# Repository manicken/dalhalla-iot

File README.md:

# Dalhalla-IoT – Modular IoT Framework

## Updates

## Overview

This is an **IoT framework** primarily targeting **ESP8266** and **ESP32** microcontrollers.  
However, the framework itself is **not bound to any specific hardware** — most of the development was actually done on **Windows (MinGW)** and later **Linux**, to take advantage of advanced debugging tools that helped isolate a **Heisenbug**.

Future candidates for porting include **Raspberry Pi Pico** and **Teensy**.

Currently, the project uses the **Arduino framework** as a base, 
but there’s essentially nothing preventing it from running **fully standalone**, 
apart from needing to provide custom drivers.

The **WiFiManager library** is used to easily flash multiple devices with firmware and register them on a network.  
This part may later evolve into something more like **Tasmota** or **ESPEasy**, simplifying device initialization.

---

## Key Features

- **Modular and lightweight architecture** 
- **HAL/DAL configuration via JSON**, mapped to an internal tree structure.
- Devices can be added/removed **without firmware rebuild** or even restarting the system.
- Unified **device abstraction layer** — each device has a unique **UID** (8-character ASCII, mapped internally to `uint64_t` for fast access).
- All devices derive from a common `Device` base class with virtual functions.
- Optional **Device Capabilities interface** planned to auto-generate documentation for each device in the GUI.

---

## JSON Configuration

Configuration is hierarchical (tree-based), supporting both **physical** and **logical/virtual** devices.

- Address paths use `:` (colon) as a separator — safe for HTTP URLs.
- Example:  
  `root:1wire:sensor1:temp`

### Example: 1-Wire Bus Groups

- Multiple 1-Wire buses can be grouped.
- Supports synchronized measurements across sensors:
  - Send `start measure` to all devices.
  - Wait defined interval.
  - Read all values simultaneously.
- Supports `refreshTime` per group or per individual device.

---

## Core Data Types

### `HALValue`
A generic type handling integers, unsigned integers, and floats consistently, simplifying read/write/compare logic.

### `ZeroCopyString`
A custom lightweight string type (similar to `std::string_view`) with additional utility:
- `SplitOffHead(char delimiter)` – substring extraction without copying.
- Direct numeric conversion (`int32`, `uint32`, `float`).
- Hex values (`0x` prefix) auto-detected.
- Used extensively to minimize heap fragmentation.

---

## Script Engine

Inspired by **ESPEasy Rules**, with plans for **event-driven execution** (not yet fully implemented, it's in a beta stage).

Scripts interact with devices via their UIDs, as defined in the JSON configuration.

**Syntax Highlights:**
- Conditionals (`if`, `then`, `elseif`, `else`, `endif`)
- Event blocks (`on`, `endon`) — planned.
- Newlines normalized to `\n`
- Supports `//` and `/* ... */` comments.
- Identifiers may include letters, digits, `_ : #`
- Numbers recognized automatically (`int`, `float`, hex).

**Example reserved keywords:**  
`if, then, do, elseif, else, endif, on, endon`

**Virtual devices** act as internal variables for flexible data handling.

---

## File Handling & Configuration Reload

- **Web-based file management** via FSBrowser for editing config and scripts.
- `CommandExecutor` (`DALHAL_CommandExecutor.cpp`) handles:
  - Config/script reload
  - Device commands
  - External access via Serial/WebSocket

### Websocket (port 82)/Serial(UART) API
Please note that the old REST API has been deprecated because its synchronous structure is incompatible with AsyncWebServer. In the future, it might be possible to make it work using the standard synchronous WebServer.

However the new Websocket API is accessed on <deviceIP>:82/ws but <deviceIP>:82 provides a simple built in GUI for basic needs

| Endpoint | Description |
|-----------|-------------|
| `hal/reloadcfg` | Reload HAL configuration |
| `hal/scripts/reload` | Reload scripts |
| `hal/scripts/start` | Start script execution |
| `hal/scripts/stop` | Stop scripts |
| `hal/getAvailableGPIOs` | List GPIOs |
| `hal/printDevices` | Print all devices |
| `hal/printLog` | Show system log |
| `hal/exec/<device_uid>` | Execute command on device |
| `hal/read/<type>/<device_uid>/<cmd>` | Read from device |
| `hal/write/<type>/<device_uid>/<value>` | Write to device |
| `system/info` | Get System Info |
| `system/reset` or `system/restart` | Execute a system restart |
| `ver` | gets build version, is not currently not updated regulary as the software is still in major development |
| `help` | Show the whole command tree |

**Types:** `bool`, `uint`, `float`, `string`, `json`  
**Device-specific commands:** e.g. read `temp` from DHT sensor.

### Windows Environment
Uses a **command loop thread** to dispatch commands to the `CommandExecutor`.

---

## Architecture Details

### Timers

Uses a modified version of **TimeAlarms**, supporting:
- Individual parameter sets per alarm.
- Safe parameter casting using `OnTickExtParameters` base class.

> https://github.com/manicken/TimeAlarms

---

## Memory Optimization and Heap Management

### JSON Loading Process
1. File read into `const char*` buffer (for zero-copy parsing via ArduinoJSON).
2. JSON document created with 1.5× file size buffer.
3. Validation ensures all mandatory fields exist.
4. Valid entries counted, marked, and loaded into an internal device array.
5. Deallocation of buffer and JSON document.

Although pointer arrays help reduce fragmentation, complete deallocation leaves large gaps (“holes”).  
A potential future solution is to convert configuration into **BSON** to allow direct loading without reallocation.

### Script Loading
- All active scripts validated sequentially.
- Only valid scripts loaded into memory for execution.
- Comments stripped before memory allocation.
- Validated scripts compiled into optimized, pre-tokenized structures for fast runtime execution.

---

## Example Files

- **HAL config example:**  
  [hal_cfg.json](https://github.com/manicken/dalhalla-io/blob/main/hal_cfg.json)
- **TimerAlarms config example:**  
  [template.json](https://github.com/manicken/dalhalla-io/blob/main/template.json)
- **Script example:**  
  [script1.txt](https://github.com/manicken/dalhalla-io/blob/main/script1.txt)

---

## Webbased WiFi configurator

[Available here](https://github.com/manicken/dalhalla-iot/tree/main/InitialCfgGui)

- Introduces a HTML + JavaScript tool as an alternative to the AP-based web portal.
- Works in Chromium-based browsers (Edge, Opera, Chrome, etc.).
- Enables configuration of Wi-Fi settings and credentials via USB-serial connection, without needing to connect to the device's AP.
- **Log output:** displays messages printed by the device in real-time.
- **Command input:** allows sending commands directly to the device.

This provides a more flexible option for local setup and testing.

## Licensing

The project currently uses **GPLv3**, to ensure it remains **fully open-source**.  
However, device registries for `root` and `i2c` are under **MIT license**, allowing third-party device extensions without forced disclosure.

Open for discussion whether the entire project should remain GPLv3 or switch fully to MIT.

---

## Future Plans

- Full event-driven script execution (beta state)
- MQTT and WebSocket(implemented) command sources.
- More advanced web UI for configuration and file management.
- Optional BSON configuration storage to eliminate heap fragmentation.
- Extended device capability introspection and GUI auto-documentation (is in a beta stage).

---

## Purpose

> The main goal is to provide a **flexible architecture for IoT devices**,  
> where configuration and logic can be changed **without recompilation**.

**dependencies**<br>
special version of TimeAlarms<br>
that can have any amount of alarms (up to 255)<br>
and also can use parameters when calling handler functions<br>
note. this dependency is included in platformio.ini and is automatically installed<br>
https://github.com/manicken/TimeAlarms <br>

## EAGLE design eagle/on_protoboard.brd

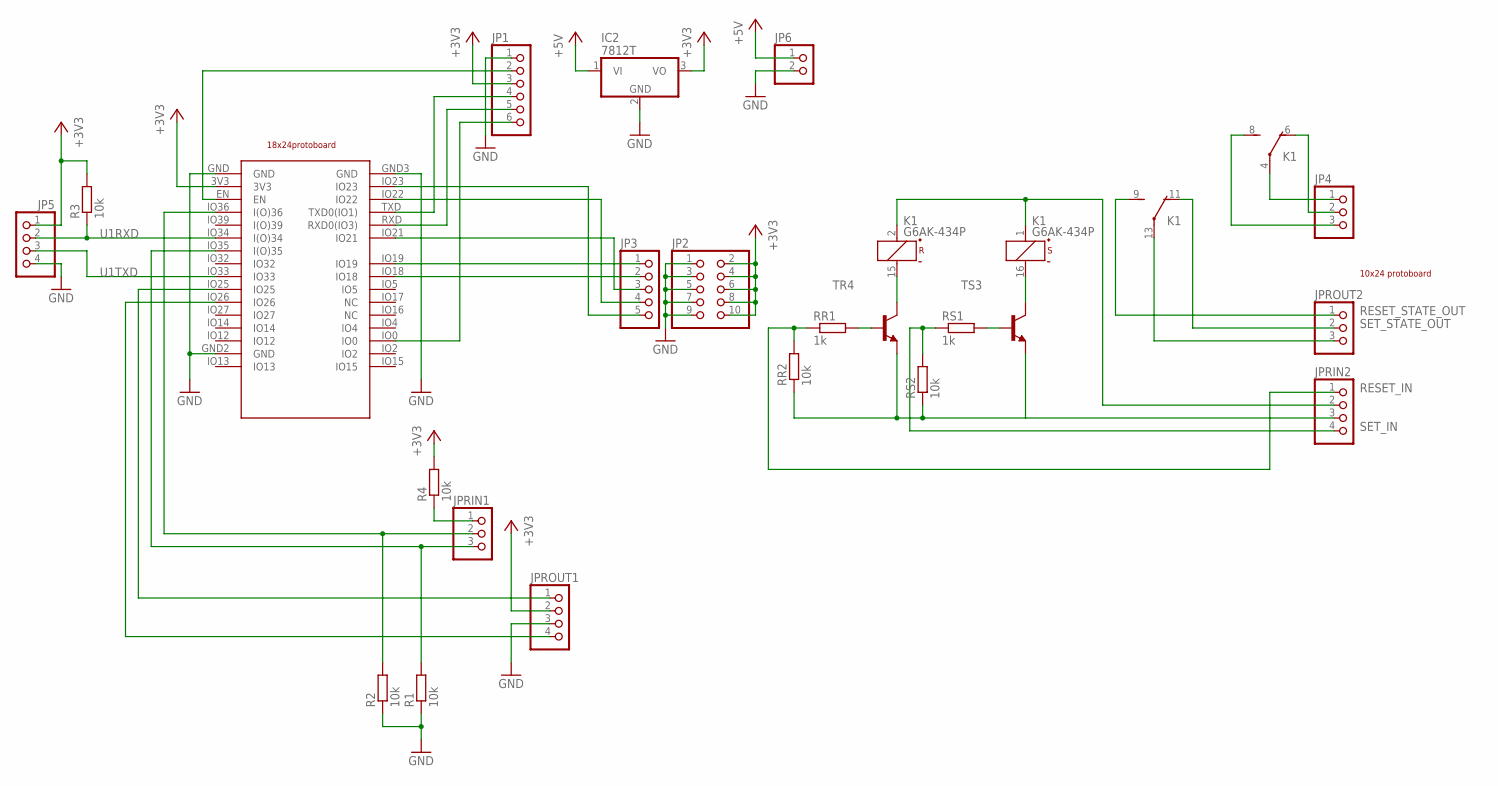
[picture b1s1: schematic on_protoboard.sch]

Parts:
ESP-32S-ADAPTER-PCB1: ESP-32S-ADAPTER-BREAKOUT; ESP-32S-ADAPTER-PCB
IC2: 7812T; TO220H
JP1: PINHD-1X6/90; 1X06/90
JP2: PINHD-2X5; 2X05
JP3: PINHD-1X5; 1X05
JP4: PINHD-1X3; 1X03
JP5: PINHD-1X4; 1X04
JP6: PINHD-1X2; 1X02
JPRIN1: PINHD-1X3; 1X03
JPRIN2: PINHD-1X4; 1X04
JPROUT1: PINHD-1X4; 1X04
JPROUT2: PINHD-1X3; 1X03
K1: G6AK-434P
R1, R2, R3, R4: 10k; R0603
RR1: 1k; R0603
RR2: 10k; R0603
RS1: 1k; R0603
RS2: 10k; R0603
TR4: -NPN-TO92-EBC; TO92-EBC
TS3: -NPN-TO92-EBC; TO92-EBC
U$1: 18X24; PROTOBOARD_18X24_HOLE
U$2: 10X24; PROTOBOARD_10X24_HOLE

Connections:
+3V3: ESP-32S-ADAPTER-PCB1.3V3, IC2.3 (VO), JP1.3, JP2.2, JP2.4, JP2.6, JP2.8, JP2.10, JP5.1, JPROUT1.2, R3.2, R4.2
+5V: IC2.1 (VI), JP6.1
GND: ESP-32S-ADAPTER-PCB1.GND, ESP-32S-ADAPTER-PCB1.GND2 (GND), ESP-32S-ADAPTER-PCB1.GND3 (GND), IC2.2 (GND), JP1.1, JP2.1, JP2.3, JP2.5, JP2.7, JP2.9, JP5.4, JP6.2, JPROUT1.3, R1.1, R2.1
unnamed: ESP-32S-ADAPTER-PCB1.EN, JP1.2
unnamed: JPRIN2.2, K1.1 (+), K1.2 (+)
unnamed: ESP-32S-ADAPTER-PCB1.TXD (TXD0(IO1)), JP1.4
unnamed: ESP-32S-ADAPTER-PCB1.RXD (RXD0(IO3)), JP1.5
unnamed: K1.15 (-), TR4.C
unnamed: ESP-32S-ADAPTER-PCB1.IO0, JP1.6
unnamed: K1.16 (-), TS3.C
unnamed: RS1.2, TS3.B
unnamed: JPRIN2.3, RR2.1, RS2.1, TR4.E, TS3.E
unnamed: JPROUT2.3, K1.13
unnamed: RR1.2, TR4.B
unnamed: ESP-32S-ADAPTER-PCB1.IO19, JP3.1
unnamed: ESP-32S-ADAPTER-PCB1.IO18, JP3.2
unnamed: ESP-32S-ADAPTER-PCB1.IO21, JP3.3
unnamed: JP4.1, K1.4
unnamed: JP4.3, K1.8 (S)
unnamed: ESP-32S-ADAPTER-PCB1.IO22, JP3.4
unnamed: ESP-32S-ADAPTER-PCB1.IO35 (I(O)35), JPRIN1.3, R1.2
unnamed: JP4.2, K1.6 (O)
unnamed: ESP-32S-ADAPTER-PCB1.IO36 (I(O)36), JPRIN1.2, R2.2
unnamed: ESP-32S-ADAPTER-PCB1.IO23, JP3.5
unnamed: JPRIN1.1, R4.1
unnamed: ESP-32S-ADAPTER-PCB1.IO25, JPROUT1.1
unnamed: ESP-32S-ADAPTER-PCB1.IO26, JPROUT1.4
RESET_IN: JPRIN2.1, RR1.1, RR2.2
RESET_STATE_OUT: JPROUT2.1, K1.9 (S)
SET_IN: JPRIN2.4, RS1.1, RS2.2
SET_STATE_OUT: JPROUT2.2, K1.11 (O)
U1RXD: ESP-32S-ADAPTER-PCB1.IO34 (I(O)34), JP5.2, R3.1
U1TXD: ESP-32S-ADAPTER-PCB1.IO33, JP5.3

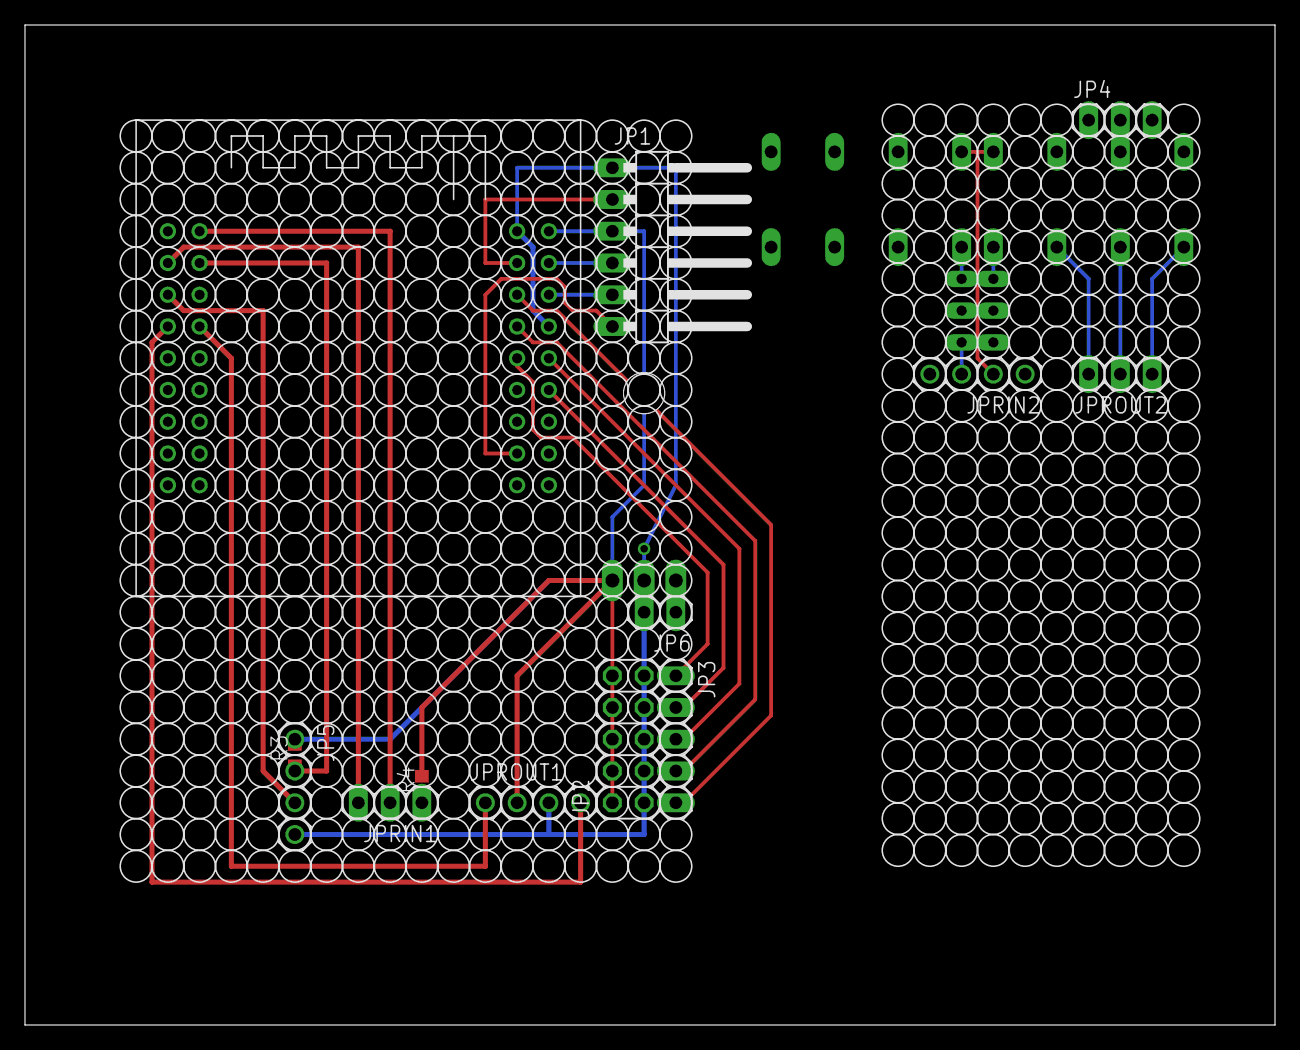
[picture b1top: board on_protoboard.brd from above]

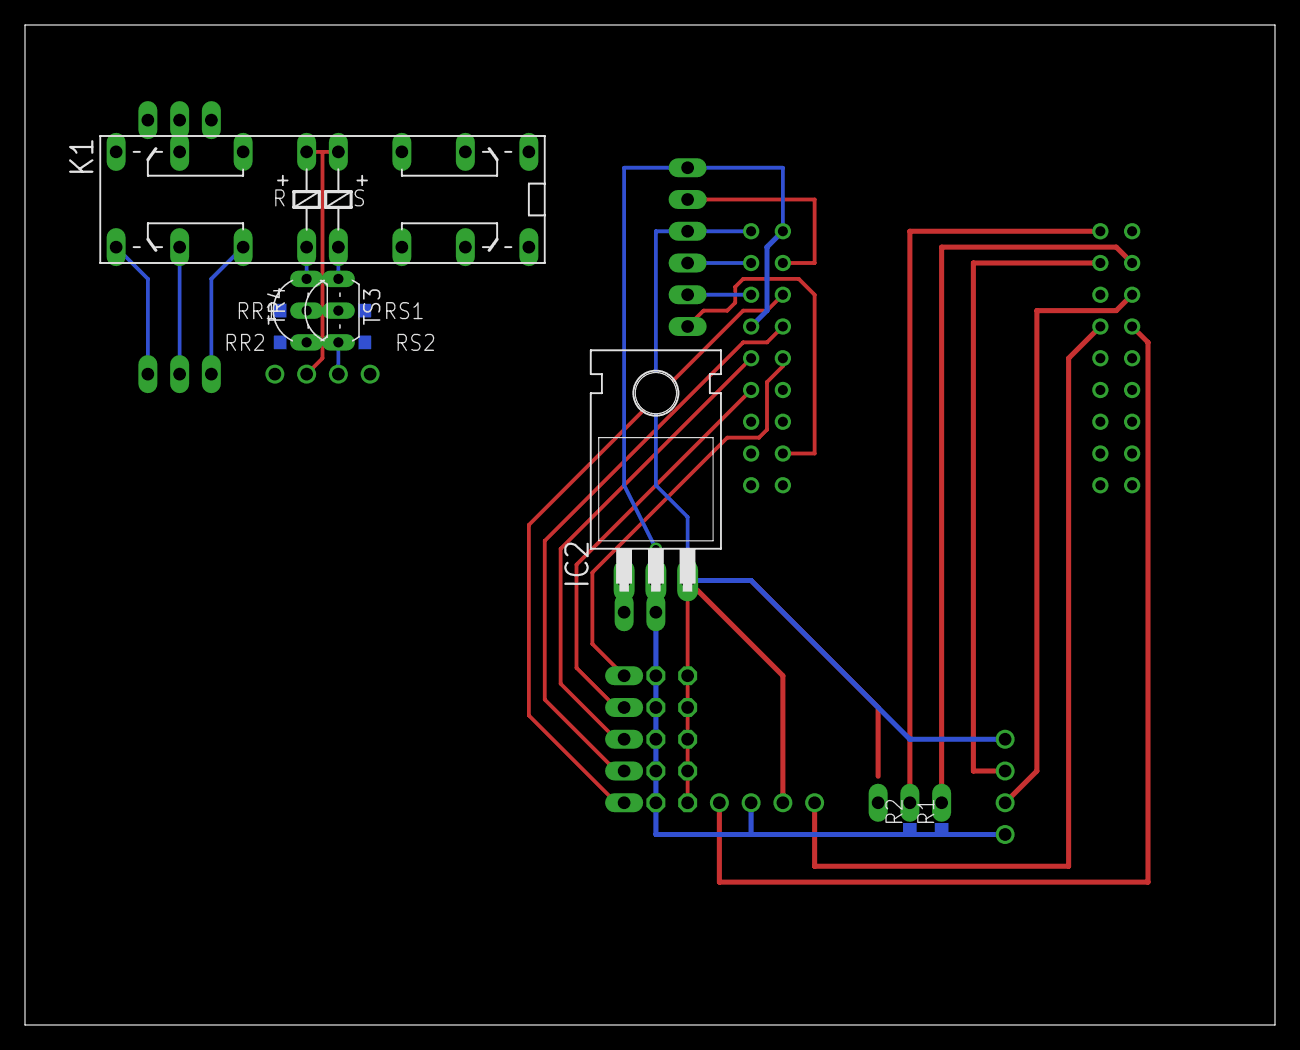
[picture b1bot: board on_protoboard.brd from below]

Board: 2 copper layers, 100.0 x 80.0 mm, 25 parts (10 on the bottom side), 33 nets.

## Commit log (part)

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2025-09-23 add I2C device name resolution for scanner
2025-09-26 scripts list.txt can now be used to define which scripts to load, if not found then script1.txt is default
2025-09-26 disabled scripts list file reading/parsing for now as there is a bug somewhere
2025-09-29 Multiscript using list.txt is now available, note default scriptname is now script.txt
2025-09-30 performance optimizations
2025-09-30 templated ParseAndTokenize have now replaced StripComments, CountTokens and Tokenize for better code maintainbility
2025-10-01 Rename Token(s) to ScriptToken(s) and make separate Token that only have col line the inherit line: ZeroCopyString->Token->ScriptToken
2025-10-01 Separating out Action and Conditions related code to own files
2025-10-01 Move all Parser and Runtime related files to subfolders
2025-10-02 non blocking startup when wifi connection fail+better webtoolui+serial halcmdexec
2025-10-28 begin working on ExtractAssignmentParts to allow func call statements
2025-11-03 refactoring cleaner code, begin to add remote fetch REST virtual device
2025-11-04 begin to work with allowing [] accessors in script engine
2025-11-06 This update removes the old CachedDeviceAccess system and introduces the lighter CachedDeviceRead implementation.
2025-11-06 Update README to include InitialCfgGui comment
2025-11-13 Fixed win_sim stubs so i can begin to work with HomeAssistant implementation using PubSubClient
2025-11-15 Futher implementations of HASS
2025-11-16 HA ++
2025-11-18 HASS ++
2025-11-19 HA Sensor entity done
2025-11-20 implement access to Hass jsonRoot so that for example device UID can be passed or other global settings
2025-11-20 uniform status state deviceuid generation
2025-11-26 fix PubSubClient so that it compiles on pc sim + other bugfixes
2025-11-27 HASS switch/button/sensor now works
2025-11-28 Fix HA device so it allow subdevices (actually type error), plus fixed Device::findInArray (device array) so when device are set to not having sub dev. and the path given has many it generate error
2025-12-01 CommandExecutor: remove usage of Request structs, error report on operation not success using device type, change to use GlobalLogger for errors
2025-12-02 cb null check
2025-12-03 better findDevice function
2025-12-03 implemented the event function for the template class
2025-12-04 move planned PWM_LEDC type, and included comment about placing items after RegistryTerminatorItem
2025-12-09 Made 1 wire temp and dht devices able to trigger events
2025-12-10 currently not working
2025-12-11 stable release
2026-01-14 fix small typo
2026-01-15 DCServo device add timeout functionality plus json cfg
2026-01-24 add LEDC_Servo device, TODO replace REST interface with proper WebSocket
2026-01-26 LEDC_Servo cfg add autoOffAfterMs, useNormValue then adjusted code
2026-01-28 add waveshare esp32-c6-zero support
2026-01-31 fixed HA number so that it properly sends back current value changed value on success, otherwise the old value is sent back. Also fixed the command path to use callback to be completely transparent o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
2026-02-05 Fixed Actuator naming bug, Updated ButtonInput to fretch value from targetDevice instead of storing toggle value locally, add WebSocketAPI Global Message Function
2026-02-13 prototype HASS DD removal of stale entities
2026-02-15 Actuator: change Motor to Drive to generalize, Created new device LatchingRelay (currently only feedback mode)
2026-02-15 Fix conflicts of globally used names
2026-02-17 add hass dd debug logging
2026-02-18 Add HA Sensor availability send non deadlock
2026-02-22 REGO600 driver use of RegDefine and OpCodeInfo instead of raw opcode + address, dalhal rego600 device uses regnamne instead of raw opcode + address
2026-02-26 Major code restructure and cleanup
2026-02-27 More code cleanup and creating better file folder structures
2026-02-28 Move dalhal devices into separate folders so that the Reactive implementation files can live beside, then implemented the reactive engine completely, TODO implement on all devices
2026-02-28 Some cleanup
2026-03-01 Add ReactiveHALValue that can emit event through a callback when the value is changed, then implemented ScriptVariableReactive
2026-03-03 Sort items
2026-03-04 Reactive implement on: LatchingRelay, LEDC_Servo & ThingSpeak
2026-03-04 implemented reactive @ ButtonInput
2026-03-04 change LEDC_Servo to more general PWM_Servo
2026-03-05 Begin with JSON Scheme structures, implemented static CheckOrGetDeviceEvents function TODO implement it on every device that uses Reactive
2026-03-07 Add API cmd printRegistry and cleared up system/info and gpio print, also fixed API web UI autodetect json which use details element
2026-03-11 Begin to refactor device registry
2026-03-12 Refactor to use DeviceCreateContext& context for all CreateFunctions and device constructors
2026-03-12 Maybe split Registry Base Define into DefineBase and RootDefine
2026-03-16 Begin to cleanup device .h files
2026-03-17 Finished Json Schema Validator, remove obsolete UseRootUID flag and usage of special type Register::DefineRoot
2026-03-18 PWM Servo Json Scheme almost done, TODO need special FieldConstraint so that i can compare two values
2026-03-19 Schema now validate Constraints
2026-03-19 Add more json schemes
2026-03-24 Fix more JsonSchemes for Script/RF433 devices
2026-03-25 REGO600 device JsonScheme done
2026-03-25 cleanup - removed comments related to ::VerifyJSON
2026-03-25 Homeassistant json scheme done
2026-03-25 remove all usage of old ValidateJSON functions, and all reg fields
2026-03-27 Can now print whole schema to the WebsocketClient as a json to use with future gui
2026-04-01 change PinFunctions into constexpressions inside a namespace PinFunc for much easier usage
2026-04-02 Split out and improved FieldString variants
2026-04-04 Now Script Events are working
2026-04-07 start to fix pc simulation code port
2026-04-08 Added additional info on JsonSchema Validations
2026-04-08 Fixed annoying bug that did happend when using virtual schema fields groups
2026-04-14 Begin to implement the new schema type structures
2026-04-14 Begin to implement the new schema type structures ++2
2026-04-15 chore: reorganize project file structure for JSON schema types + typo fix
2026-04-16 minor cleanup
2026-04-19 Progress on Schema ToJson using the new structures
2026-04-21 Optimize the generated Schema Json
2026-04-22 refactor to use the new schemadriven value extractors
2026-04-25 Refactor schema extraction: add instance-based extractors and remove static dispatch usage. Implemented on more devices
2026-04-27 fix init order problem with i2c master, plus implemented websocket system/EnterRecoveryMode command that executes directly as a failsafe against main loop locks
2026-04-29 refactor HALValue: removed as<type> replaced it with to<type> and asRaw<type> also did refactor of whole HALValue to make it consistent + added new WiFiConnection manager
2026-05-04 Make GPIO_Manager cleaner + introduced pin reservation types so that static pin reservations can be done
2026-05-06 Refactor PubSubClient to streaming RX architecture
    - Split header/payload parsing
    - Add header + complete callbacks
    - Replace std::function with function pointers + context
    - Add structured error handling
    - Reduce RAM and flash usage
2026-05-07 Refactor to use the new PSC beginPublish_fmt, lastTxTopic and lastTxTopicLength functions, inside DD Send
2026-05-13 Fix when and how HASS subscribes to topics, this fixes alot of issues
2026-05-19 Refactor - Remove use of TopicBasePath Refactor - now only storing a std::string for the hass_uid Refactor - add HALValue Printer helper to use with the Print class Refactor - Change into using new f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
2026-05-20 forgot to read hass_uid into the instance string
2026-05-21 Fix so that 1wire temp and DHTxx devices use a dataValid flag to signal when they have actually read a valid value
2026-05-21 add failsafe reset rest cmd
2026-05-22 Refactor and bug fixes * Move OTA start out of ArduinoOTA wrapper OTA.h OTA.cpp * fix data extraction bug in RF433 driver where expected uint but tried convert to const char* * Fix so that value chec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
2026-05-27 Refactor
    * Added virtual const Registry::DefineBase* GetRegistryDefine();
    this is gonna be used to get the define from a instance directly
    without the need to do a second lockup using the type
    used to fetch the sirect access function ptrs to use in CachedDeviceAccess and CachedDeviceRead
    can also be used to fetch help by only giving the device uid
    * added expected value type given to general HALValue read/write functions
2026-05-29 Wrap device registries in a struct DeviceRegistry { const Registry::Item* items; const size_t count; const char* name; const char* path; constexpr DeviceRegistry(const Registry::Item* items, const si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
    start to implement WebSocket_StreamWriter to use with the API CLI functions
    it's also to be used with the upcoming cfg editor GUI
2026-06-02 move DALHAL_ReactiveConfig delete config folder as it makes autocomplete hard while typing co to get core Split StreamWriter into StringBuilderStreamer and BlockStreamer for better separation so that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
2026-06-03 Refactor to use StringBuilderStreamer everywhere i create huge strings to be consumed by API
2026-06-04 Major refactor where all Devices: String ToString() are replaced with void PrintTo(StringBuilderStreamer& sbs) for absolute heap free allocations and fragmentation
2026-06-04 now have the following: static bool Broadcast(const char* msg, size_t len, CmdCbType type = CmdCbType::Control); static bool Broadcast(std::string &msg, CmdCbType type = CmdCbType::Control); // to be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
    changed:
    void Logger::EmitLastEntry()
    {
2026-06-04 cleanup
2026-06-08 Fix ArduinoJSON.h to proper ArduinoJson.h to make it compile on linux OS , also make sure to include ArduinoJson.h where its used to avoid include creep
2026-06-10 Template device now have all possible By FunctionName Table examples
2026-06-10 All devices that have functions by name now have Function vs Name Lockup Tables implemented 1 wire temp device and bus have own Registry defines for future proof structures and to avoid sharing data 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
2026-06-11 Remove CLI-specific virtual Device command handlers in favor of function tables
    Replace legacy Device virtual read/write/exec CLI entry points with function-table dispatch.
    Rename exec(ZeroCopyString) (previously only used by Home Assistant) to ha_apply to clarify intent as an external state update hook.
2026-06-11 Refactor CommandExecutor into hierarchical command tree dispatcher
    - Replace flat/virtual command handling with static constexpr command tree
    - Introduce recursive node-based command resolution (ExecuteNode)
    - Split command parsing into structured path (type/uid/cmd/params)
    - Standardize HAL read/write execution through function tables
    - Centralize device capability lookup via GetDeviceFunction
    - Add recursive help printer based on command tree traversal
2026-06-17 --- Major refactor --- Introduced new FunctionTable macros to make everything tidy: - DALHAL_FUNCTION_ENTRY(name, fn, help) { CE_MATCH_EMIT_STR(name), &fn, CE_EMIT_STR(help) } - DALHAL_FUNCTION_ENTRY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
    Removed/Replaced all previous used device exec/read/write functions
    with new FunctionTable en
2026-06-19 Moved Script/Device Trigger Validate function from DeviceManager to DALHAL_SCRIPT_ENGINE_Parser_Triggers
2026-06-19 TODO make script exec() function work again
2026-06-23 fix script load framing bug
2026-06-25 Add WebSocket CLI API with MCU-driven autocomplete and command flags
    - Autocomplete help generated from MCU help system
    - Command tree now supports flags:
    - hide entries from CLI help
    - GUI flag for fast-access button generation in WS interface
    - Add built-in WiFi setup modal
